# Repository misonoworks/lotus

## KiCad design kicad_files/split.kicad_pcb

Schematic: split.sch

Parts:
D1, D2, D3, D4, D5, D6, D7, D8, D9, D10, D11, D12, D13, D14, D15, D16, D17, D18, D19, D20, D21, D22, D23, D24, D25, D26, D27, D28, D29, D30, D31, D32, D33, D34, D35, D36, D37, D38, D39, D40, D41, D42, D43, D44, D45, D46, D47, D48: D_Small; D_DO-34_SOD68_P7.62mm_Horizontal
EX1, EX2, EX3, EX4: MX-NoLED; CherryMX_Choc_1u
J1, J2: Conn_01x04_Female; PinHeader_1x04_P2.54mm_Vertical
J3: HALF_L_IO; MJ-4PP-9_1side
J4: HALF_R_IO; MJ-4PP-9_1side
J5: PANEL_L_OUTPUT; MJ-4PP-9_1side
J6: PANEL_R_OUTPUT; MJ-4PP-9_1side
J7: PANEL_R_INPUT; MJ-4PP-9_1side
J8: PANEL_L_INPUT; MJ-4PP-9_1side
MX1, MX2, MX3, MX4, MX5, MX6, MX8, MX9, MX10, MX11, MX12, MX13, MX15, MX16, MX17, MX18, MX19, MX20, MX22, MX23, MX24, MX25, MX26, MX27, MX29, MX30, MX31, MX32, MX33, MX34, MX35, MX36, MX37, MX38, MX39, MX40, MX43, MX44, MX45, MX46: MX-NoLED; CherryMX_Choc_1u
MX7, MX14: MX-NoLED; MX-Alps-Choc-1U
MX21, MX28, MX41, MX42, MX47, MX48: MX-NoLED; CherryMX_Choc_1.5u
SW1, SW2: Rotary_Encoder_Switch; RotaryEncoder_Alps_EC11E-Switch_Vertical_H20mm
SW3, SW4: Rotary_Encoder; RotaryEncoder_Alps_EC11E-Switch_Vertical_H20mm
U1, U2: ProMicro; ProMicro_v3.5

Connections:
+5V: J1.3, J3.D, J5.D, J8.D, U1.21 (VCC)
DL: J3.C, U1.2 (RX1/D2)
DR: J4.C, U2.2 (RX1/D2)
GND: EX1.1, EX2.1, J1.4, J3.A, J5.A, J8.A, SW1.C, SW3.C, U1.3 (GND), U1.4 (GND)
GNDA: EX3.1, EX4.1, J2.4, J4.A, J6.A, J7.A, SW2.C, SW4.C, U2.3 (GND), U2.4 (GND), U2.23 (GND)
LD+: SW1.A, U1.7 (4/D4)
LD-: SW1.B, U1.8 (5/C6)
unnamed: D1.2 (A), MX1.2
unnamed: D2.2 (A), MX2.2
unnamed: D3.2 (A), MX3.2
unnamed: D4.2 (A), MX4.2
unnamed: D5.2 (A), MX5.2
unnamed: D6.2 (A), MX6.2
unnamed: D7.2 (A), MX7.2, SW1.S1
unnamed: D8.2 (A), MX8.2
unnamed: D9.2 (A), MX9.2
unnamed: D10.2 (A), MX10.2
unnamed: D11.2 (A), MX11.2
unnamed: D12.2 (A), MX12.2
unnamed: D13.2 (A), MX13.2
unnamed: D14.2 (A), MX14.2, SW2.S1
unnamed: D15.2 (A), MX15.2
unnamed: D16.2 (A), MX16.2
unnamed: D17.2 (A), MX17.2
unnamed: D18.2 (A), MX18.2
unnamed: D19.2 (A), MX19.2
unnamed: D20.2 (A), MX20.2
unnamed: D21.2 (A), MX21.2
unnamed: D22.2 (A), MX22.2
unnamed: D23.2 (A), MX23.2
unnamed: D24.2 (A), MX24.2
unnamed: D25.2 (A), MX25.2
unnamed: D26.2 (A), MX26.2
unnamed: D27.2 (A), MX27.2
unnamed: D28.2 (A), MX28.2
unnamed: D29.2 (A), MX29.2
unnamed: D30.2 (A), MX30.2
unnamed: D31.2 (A), MX31.2
unnamed: D32.2 (A), MX32.2
unnamed: D33.2 (A), MX33.2
unnamed: D34.2 (A), MX34.2
unnamed: D35.2 (A), MX35.2
unnamed: D36.2 (A), MX36.2
unnamed: D37.2 (A), MX37.2
unnamed: D38.2 (A), MX38.2
unnamed: D39.2 (A), MX39.2
unnamed: D40.2 (A), MX40.2
unnamed: D41.2 (A), MX41.2
unnamed: D42.2 (A), MX42.2
unnamed: D43.2 (A), MX43.2
unnamed: D44.2 (A), MX46.2
unnamed: D45.2 (A), MX44.2
unnamed: D46.2 (A), MX45.2
unnamed: D47.2 (A), MX47.2
unnamed: D48.2 (A), MX48.2
RD+: SW2.B, U2.7 (4/D4)
RD-: SW2.A, U2.8 (5/C6)
VDD: J2.3, J4.D, J6.D, J7.D, U2.21 (VCC)
col0L: MX1.1, MX15.1, MX29.1, U1.19 (F5/A2)
col0R: MX8.1, MX22.1, MX35.1, U2.19 (F5/A2)
col1L: MX2.1, MX16.1, MX30.1, U1.18 (F6/A1)
col1R: MX9.1, MX23.1, MX36.1, U2.18 (F6/A1)
col2L: MX3.1, MX17.1, MX31.1, U1.17 (F7/A0)
col2R: MX10.1, MX24.1, MX37.1, U2.17 (F7/A0)
col3L: MX4.1, MX18.1, MX32.1, MX43.1, U1.16 (B1/15)
col3R: MX11.1, MX25.1, MX38.1, MX44.1, U2.16 (B1/15)
col4L: MX5.1, MX19.1, MX33.1, MX46.1, U1.15 (B3/14)
col4R: MX12.1, MX26.1, MX39.1, MX45.1, U2.15 (B3/14)
col5L: MX6.1, MX20.1, MX34.1, MX41.1, U1.14 (B2/16)
col5R: MX13.1, MX27.1, MX40.1, MX47.1, U2.14 (B2/16)
col6L: MX7.1, MX21.1, MX42.1, SW1.S2, U1.13 (B6/10)
col6R: MX14.1, MX28.1, MX48.1, SW2.S2, U2.13 (B6/10)
i2c_SCL_L: EX2.2, J1.2, J5.C, J8.C, SW3.B, U1.6 (3/D0/SCL)
i2c_SCL_R: EX4.2, J2.2, J6.C, J7.C, SW4.B, U2.6 (3/D0/SCL)
i2c_SDA_L: EX1.2, J1.1, J5.B, J8.B, SW3.A, U1.5 (2/D1/SDA)
i2c_SDA_R: EX3.2, J2.1, J6.B, J7.B, SW4.A, U2.5 (2/D1/SDA)
row0L: D1.1 (K), D2.1 (K), D3.1 (K), D4.1 (K), D5.1 (K), D6.1 (K), D7.1 (K), U1.9 (6/D7)
row0R: D8.1 (K), D9.1 (K), D10.1 (K), D11.1 (K), D12.1 (K), D13.1 (K), D14.1 (K), U2.9 (6/D7)
row1L: D15.1 (K), D16.1 (K), D17.1 (K), D18.1 (K), D19.1 (K), D20.1 (K), D21.1 (K), U1.10 (7/E6)
row1R: D22.1 (K), D23.1 (K), D24.1 (K), D25.1 (K), D26.1 (K), D27.1 (K), D28.1 (K), U2.10 (7/E6)
row2L: D29.1 (K), D30.1 (K), D31.1 (K), D32.1 (K), D33.1 (K), D34.1 (K), U1.11 (8/B4)
row2R: D35.1 (K), D36.1 (K), D37.1 (K), D38.1 (K), D39.1 (K), D40.1 (K), U2.11 (8/B4)
row3L: D41.1 (K), D42.1 (K), D43.1 (K), D44.1 (K), U1.12 (9/B5)
row3R: D45.1 (K), D46.1 (K), D47.1 (K), D48.1 (K), U2.12 (9/B5)

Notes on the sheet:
Left I2C Panel
Left Half
Right I2C Panel
Right Half

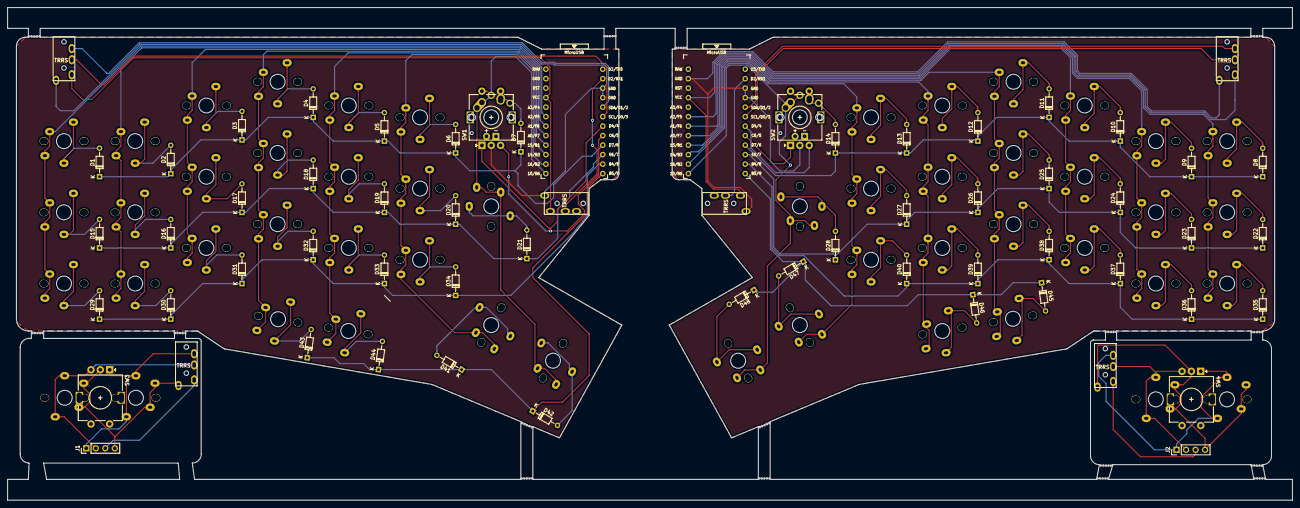
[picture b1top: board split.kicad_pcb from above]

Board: 2 copper layers, 343.7 x 131.8 mm, 114 parts (0 on the bottom side), 84 nets.
